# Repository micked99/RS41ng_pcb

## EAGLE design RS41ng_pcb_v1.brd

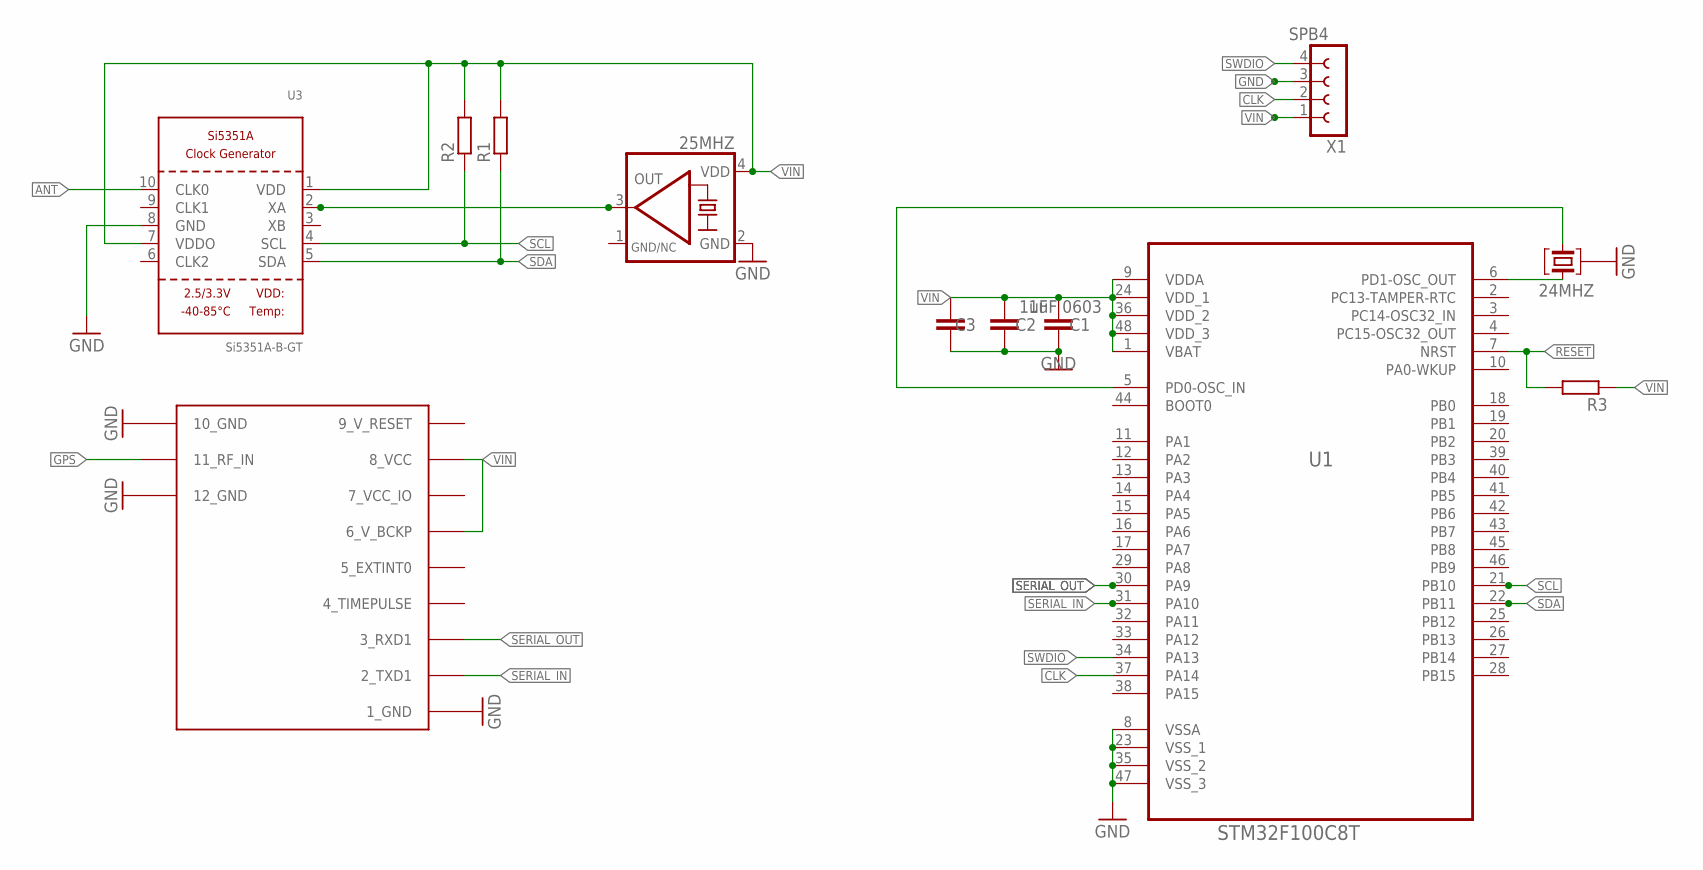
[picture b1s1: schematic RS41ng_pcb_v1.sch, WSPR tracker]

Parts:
24MHZ: 24Mhz; ABM8G
25MHZ: KXO-TCXO-CMOS-84; 3.2X2.5_KXO-84-TCXO
C1: 1uF 0603; C0603K
C2: 1uF; C0603K
C3: C-EUC1808; C1808
R1, R2, R3: R-EU_R0603; R0603
U1: STM32F100C8T; QFP50P900X900X160-48N
U3: Si5351A-B-GT; MSOP10
U$2: UBLOX_MAX
X1: SPB4

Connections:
7_VCC_IO: U$2.7_VCC_IO
9_V_RESET: U$2.9_V_RESET
ANT: U3.10 (CLK0)
CLK: U1.37 (PA14), X1.2
GND: 24MHZ.2, 24MHZ.4 (2), 25MHZ.2 (GND), C1.2, C2.2, C3.1, U1.8 (VSSA), U1.23 (VSS_1), U1.35 (VSS_2), U1.47 (VSS_3), U3.8 (GND), U$2.1_GND, U$2.10_GND, U$2.12_GND, X1.3
GND/NC: 25MHZ.1 (GND/NC)
GPS: U$2.11_RF_IN
unnamed: 24MHZ.1, U1.6 (PD1-OSC_OUT)
unnamed: 24MHZ.3, U1.5 (PD0-OSC_IN)
unnamed: 25MHZ.3 (OUT), U3.2 (XA)
RESET: R3.2, U1.7 (NRST)
SCL: R2.1, U1.21 (PB10), U3.4 (SCL)
SDA: R1.1, U1.22 (PB11), U3.5 (SDA)
SERIAL_IN: U1.31 (PA10), U$2.2_TXD1
SERIAL_OUT: U1.30 (PA9), U$2.3_RXD1
SWDIO: U1.34 (PA13), X1.4
VIN: 25MHZ.4 (VDD), C1.1, C2.1, C3.2, R1.2, R2.2, R3.1, U1.1 (VBAT), U1.9 (VDDA), U1.24 (VDD_1), U1.36 (VDD_2), U1.48 (VDD_3), U3.1 (VDD), U3.7 (VDDO), U$2.6_V_BCKP, U$2.8_VCC, X1.1

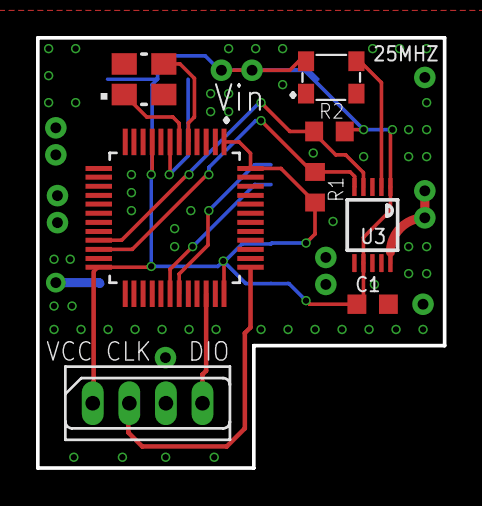
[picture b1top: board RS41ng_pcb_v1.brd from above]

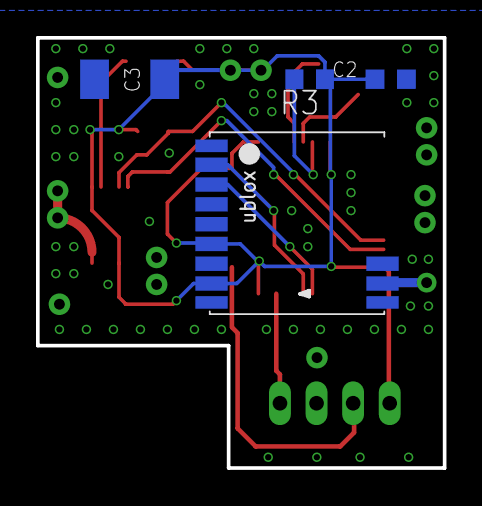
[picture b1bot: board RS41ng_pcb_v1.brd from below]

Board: 2 copper layers, 22.6 x 23.9 mm, 12 parts (4 on the bottom side), 12 nets.

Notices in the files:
parts and their libraries:
microbuilder: This work is placed in the public domain, and may be freely used for commercial and non-commercial work with the following conditions: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
crystal-geyer_V1_0: Copyright: Geyer-Electronic
